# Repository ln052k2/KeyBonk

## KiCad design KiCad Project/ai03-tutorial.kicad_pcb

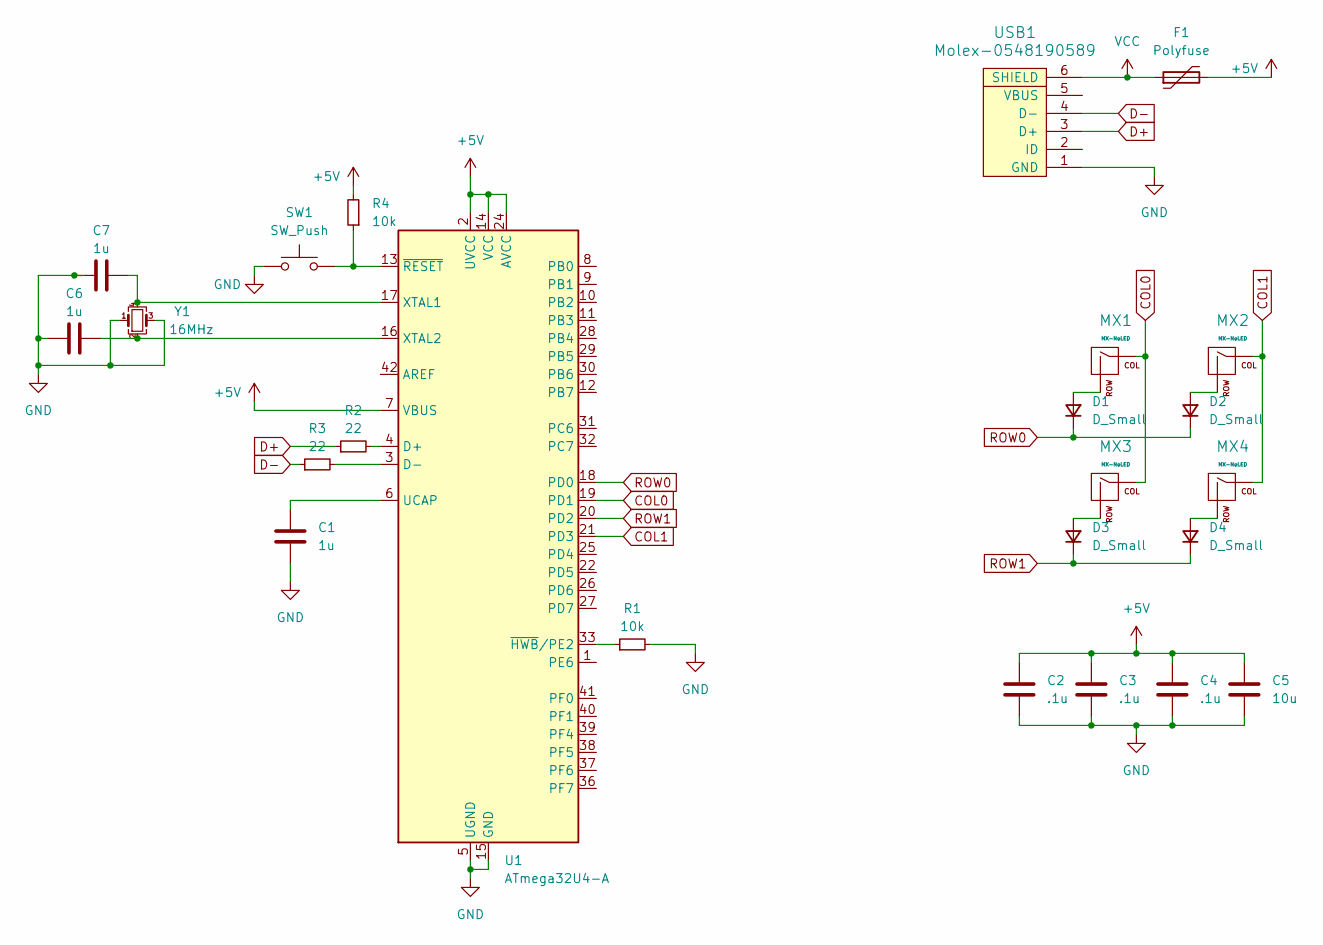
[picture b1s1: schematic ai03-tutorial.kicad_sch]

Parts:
C1, C6, C7: 1u; C_0805_2012Metric
C2, C3, C4: .1u; C_0805_2012Metric
C5: 10u; C_0805_2012Metric
D1, D2, D3, D4: D_Small; D_SOD-123
F1: Polyfuse; Fuse_1206_3216Metric
MX1, MX2, MX3, MX4: MX-NoLED; MX-1U-NoLED
R1, R4: 10k; R_0805_2012Metric
R2, R3: 22; R_0805_2012Metric
SW1: SW_Push; SKQG-1155865
U1: ATmega32U4-A; TQFP-44_10x10mm_P0.8mm
USB1: Molex-0548190589
Y1: 16MHz; Crystal_SMD_3225-4Pin_3.2x2.5mm

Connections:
+5V: C2.1, C3.1, C4.1, C5.1, F1.2, R4.2, U1.2 (UVCC), U1.7 (VBUS), U1.14 (VCC), U1.24 (AVCC), U1.34 (VCC), U1.44 (AVCC)
COL0: MX1.1 (COL), MX3.1 (COL), U1.19 (PD1)
COL1: MX2.1 (COL), MX4.1 (COL), U1.21 (PD3)
D+: R2.1, USB1.3 (D+)
D-: R3.1, USB1.4 (D-)
GND: C1.2, C2.2, C3.2, C4.2, C5.2, C6.1, C7.1, R1.2, SW1.1, U1.5 (UGND), U1.15 (GND), U1.23 (GND), U1.35 (GND), U1.43 (GND), USB1.1 (GND), Y1.1, Y1.3
unnamed: D1.2 (A), MX1.2 (ROW)
unnamed: D2.2 (A), MX2.2 (ROW)
unnamed: D3.2 (A), MX3.2 (ROW)
unnamed: D4.2 (A), MX4.2 (ROW)
unnamed: R2.2, U1.4 (D+)
unnamed: R3.2, U1.3 (D-)
unnamed: C1.1, U1.6 (UCAP)
unnamed: C7.2, U1.17 (XTAL1), Y1.4
unnamed: C6.2, U1.16 (XTAL2), Y1.2
unnamed: R1.1, U1.33 (~HWB/PE2)
unnamed: R4.1, SW1.2, U1.13 (~RESET)
ROW0: D1.1 (K), D2.1 (K), U1.18 (PD0)
ROW1: D3.1 (K), D4.1 (K), U1.20 (PD2)
VCC: F1.1, USB1.6 (SHIELD)

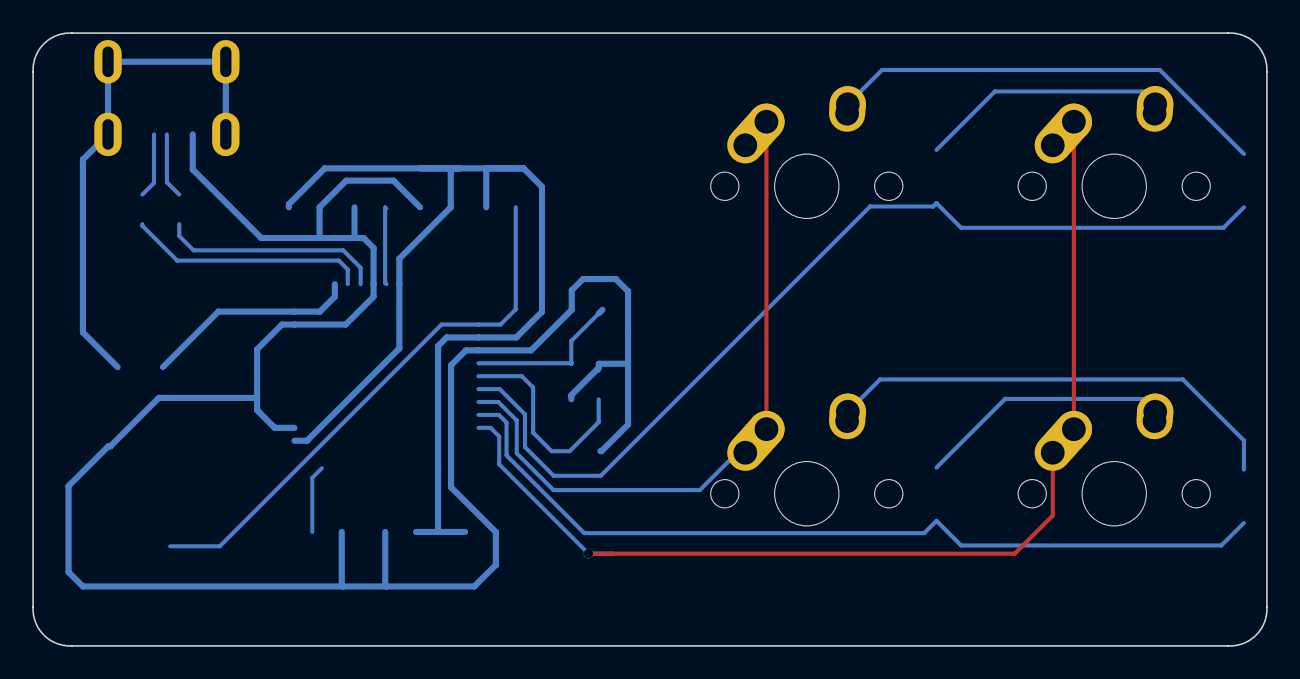
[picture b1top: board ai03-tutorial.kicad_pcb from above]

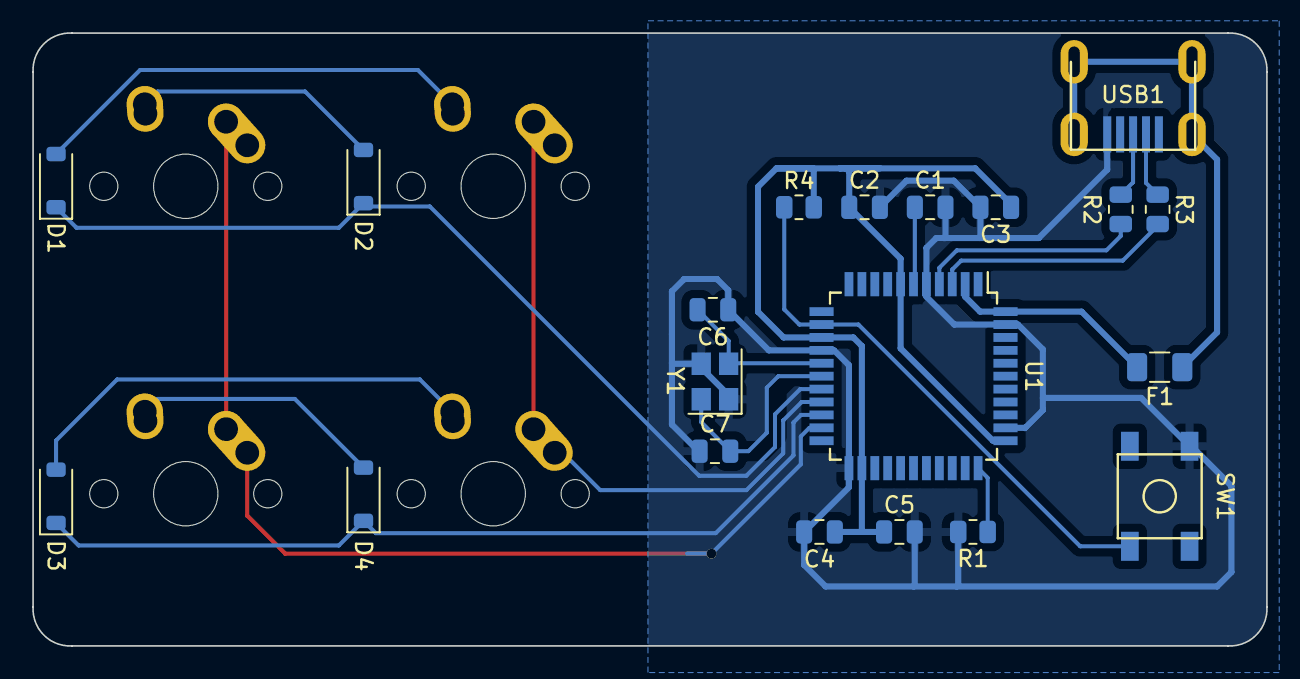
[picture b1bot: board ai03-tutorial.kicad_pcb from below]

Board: 2 copper layers, 76.5 x 38.0 mm, 24 parts (20 on the bottom side), 20 nets.

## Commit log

2023-12-14 Initial commit.
2023-12-15 Layout update.
2023-12-15 Submodules added. KiCad project created
2023-12-15 Imported footprint and model libraries
2023-12-28 Finished PCB tutorial part 3 - MCU schematic
2023-12-28 Finished PCB guide part 4 - schematic.
2023-12-28 Initial footprint and PCB layout. No traces added.
2023-12-28 Finished PCB guide part 5. Initial routing complete.
2023-12-29 Finished PCB guide part 6. Added ground copper layer.
2023-12-29 Added matrix connections.
